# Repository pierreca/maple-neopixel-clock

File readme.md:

# Maple Neopixel Clock

The goal with this clock project was to learn how to use vcarve and a Shapeoko 3 milling machine.

The electronics are from spare parts I had (I'm sure better components could be found) and the code is quickly put together to make it work but is by no means considered nice or finished.

Finally the PCB was designed to be able to plug a chronodot with an arduino nano and 3 neopixel rings and 2 buttons. I could (probably should?) have chained the rings instead of connecting them separately but didn't think about it when I designed it.

This project is unlikely to evolve or change much :)

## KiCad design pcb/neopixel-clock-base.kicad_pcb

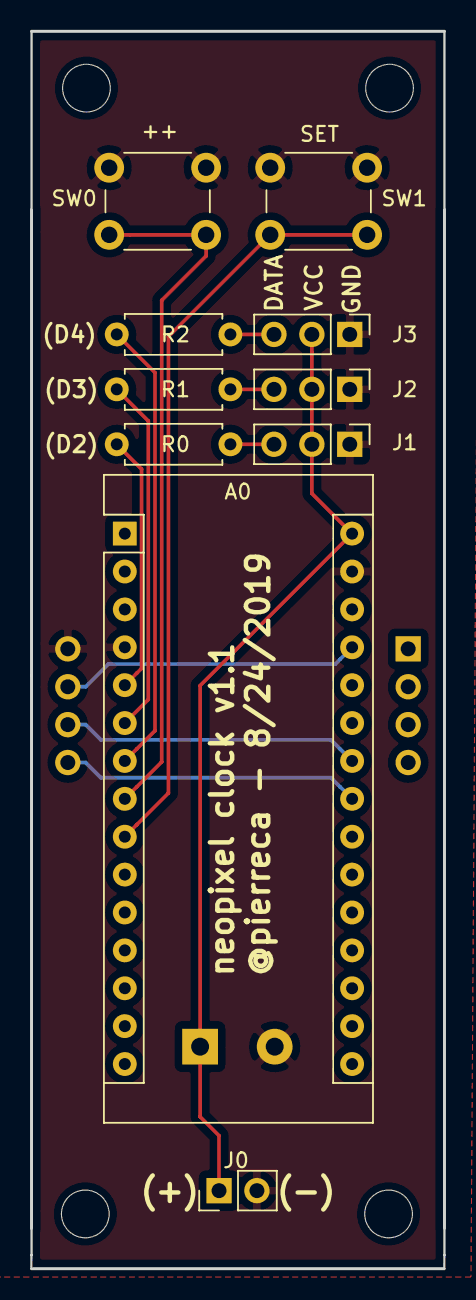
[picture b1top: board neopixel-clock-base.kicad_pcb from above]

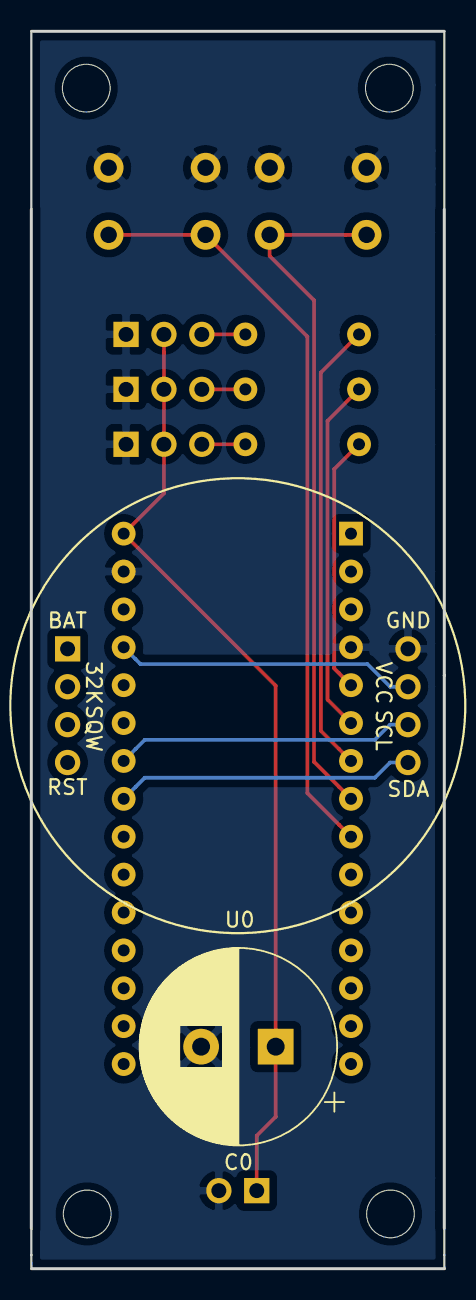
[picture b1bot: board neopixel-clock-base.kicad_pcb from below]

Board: 2 copper layers, 27.7 x 83.0 mm, 12 parts (2 on the bottom side), 13 nets.

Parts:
A0: Arduino_Nano_v3.x; Arduino_Nano
C0: 100uF 35V; CP_Radial_D13.0mm_P5.00mm
J0: Power; PinHeader_1x02_P2.54mm_Vertical
J1: Neopixel_12; PinHeader_1x03_P2.54mm_Vertical
J2: Neopixel_24; PinHeader_1x03_P2.54mm_Vertical
J3: Neopixel_60; PinHeader_1x03_P2.54mm_Vertical
R0, R1, R2: 300; R_Axial_DIN0207_L6.3mm_D2.5mm_P7.62mm_Horizontal
SW0, SW1: SW_Push; SW_PUSH_6mm
U0: Chronodot; chronodot

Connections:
GND: A0.4, A0.29, C0.2, J0.2, J1.1, J2.1, J3.1, SW0.1, SW1.1, U0.2
unnamed: A0.5, R0.2
unnamed: A0.6, R1.2
unnamed: A0.7, R2.2
unnamed: A0.8, SW0.2
unnamed: A0.9, SW1.2
unnamed: A0.23, U0.8
unnamed: A0.24, U0.6
unnamed: A0.27, U0.4
unnamed: A0.30, C0.1, J0.1, J1.2, J2.2, J3.2
unnamed: J1.3, R0.1
unnamed: J2.3, R1.1
unnamed: J3.3, R2.1

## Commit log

2019-09-03 basic code for neopixel clock + adjustments to dps badge + chronodot lib + nixie clock base
2019-09-08 Updated version of the neopixel clock code
2019-09-08 add v-carve files for cnc milling of the clock face
2019-09-08 Add base file for neopixel clock
2019-09-09 Add tabs to neopixel clock base
2019-09-09 add 2 pushbuttons to neopixel clock pcb design
2019-09-20 Add round base for neopixel clock
2019-09-24 Move schematics and PCB design into the pcb folder. Add readme and gitignore files
2019-10-07 Add prototype code to set the time using buttons
2019-11-30 Add laser-cutter pattern for acrylic rings
